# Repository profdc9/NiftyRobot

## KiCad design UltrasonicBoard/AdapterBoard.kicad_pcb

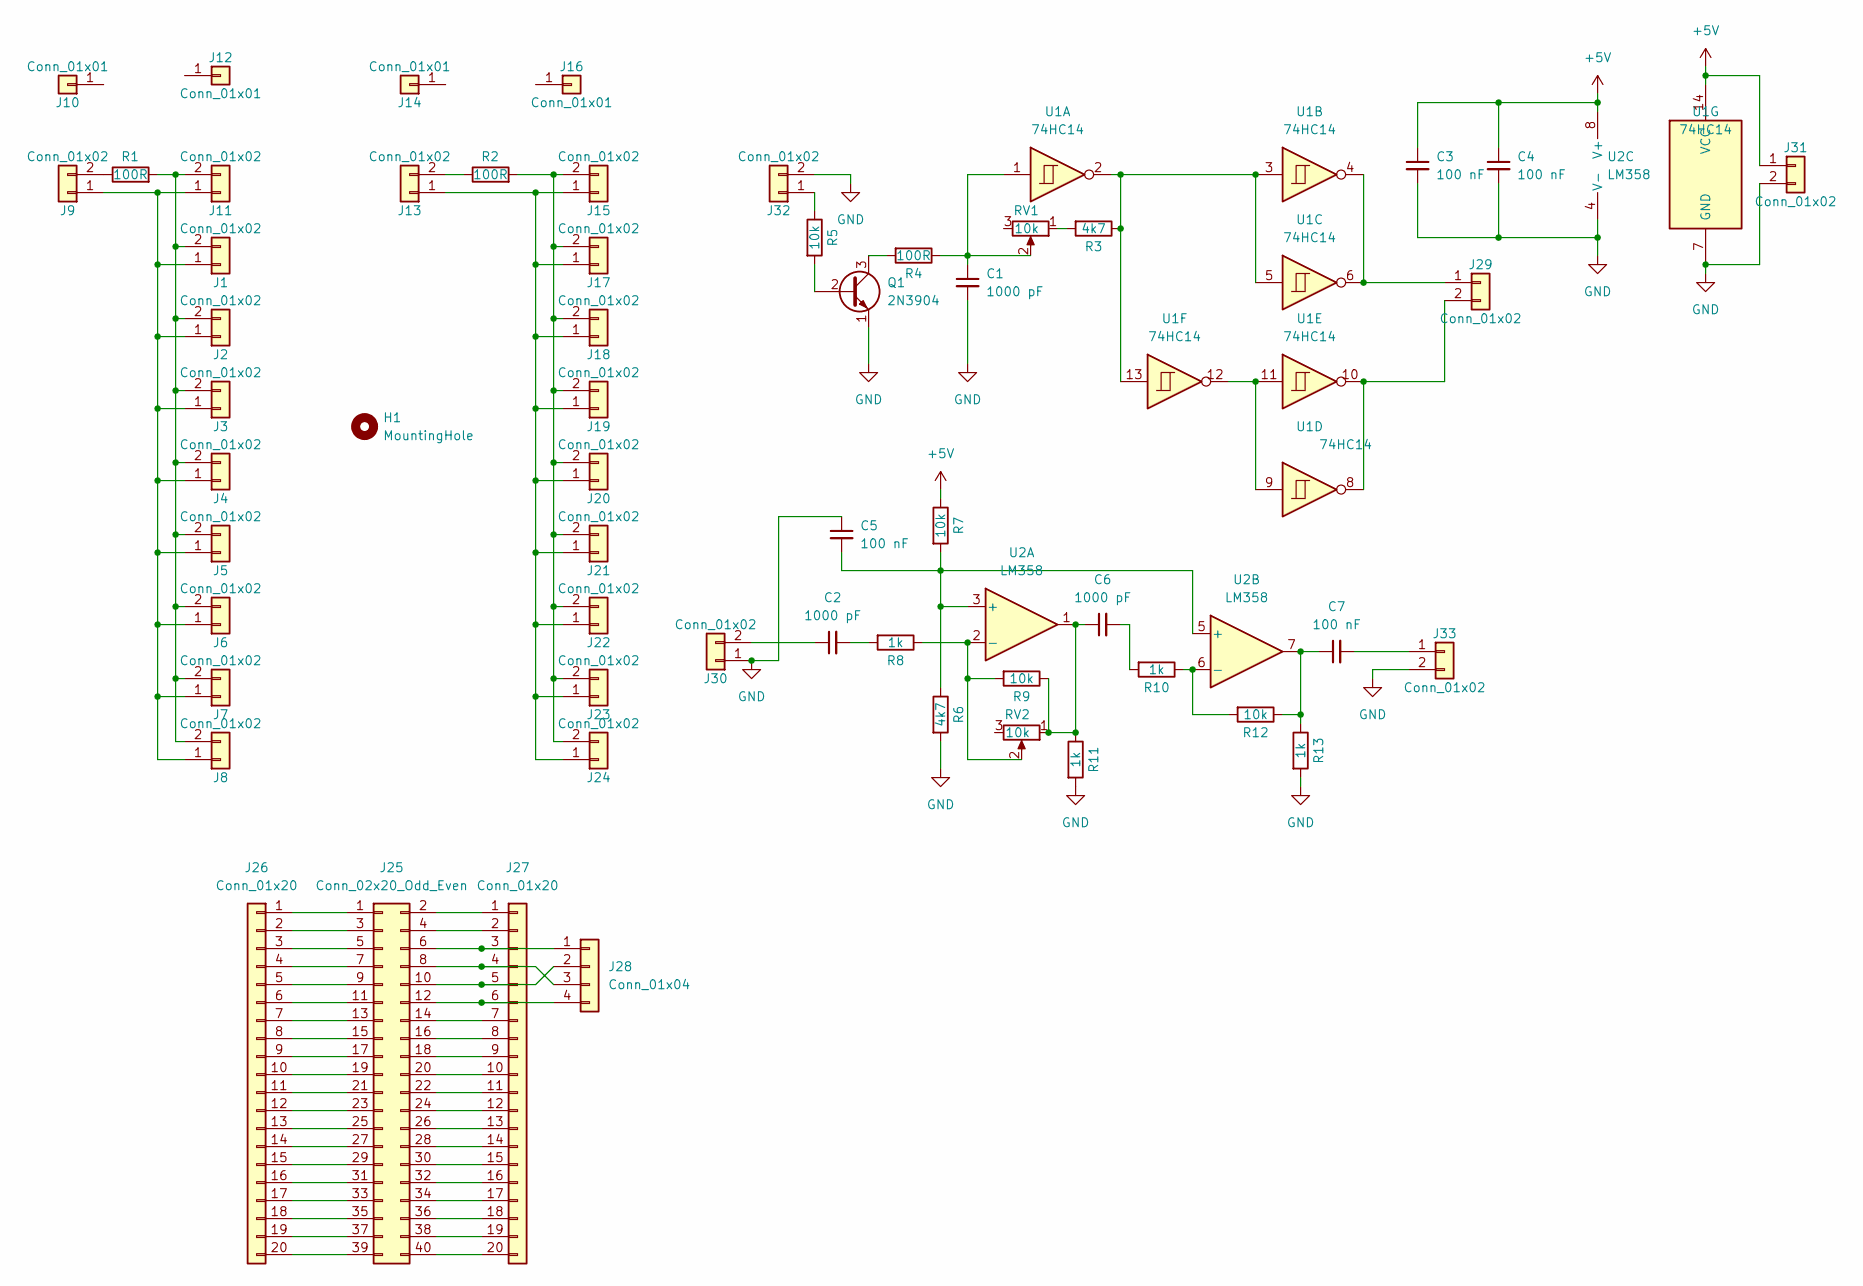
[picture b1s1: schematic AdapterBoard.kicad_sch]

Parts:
C1, C2, C6: 1000 pF; C_Disc_D5.0mm_W2.5mm_P5.00mm
C3, C4, C5, C7: 100 nF; C_Disc_D5.0mm_W2.5mm_P5.00mm
H1: MountingHole; BigSlotSeparator
J1, J2, J3, J4, J5, J6, J7, J8, J11, J15, J17, J18, J19, J20, J21, J22, J23, J24: Conn_01x02; UltrasoundTransceiver
J9, J13: Conn_01x02; TerminalBlock_bornier-2_P5.08mm
J10, J12, J14, J16: Conn_01x01; BlankMountingHole3.2
J25: Conn_02x20_Odd_Even; PinSocket_2x20_P2.54mm_Vertical
J26, J27: Conn_01x20; PinSocket_1x20_P2.54mm_Vertical
J28: Conn_01x04; PinSocket_1x04_P2.54mm_Vertical
J29, J30, J31, J32, J33: Conn_01x02; PinHeader_1x02_P2.54mm_Vertical
Q1: 2N3904; TO-92_Inline_Wide
R1, R2: 100R; R_Axial_DIN0414_L11.9mm_D4.5mm_P15.24mm_Horizontal
R3, R6: 4k7; R_Axial_DIN0207_L6.3mm_D2.5mm_P7.62mm_Horizontal
R4: 100R; R_Axial_DIN0207_L6.3mm_D2.5mm_P7.62mm_Horizontal
R5, R7, R9, R12: 10k; R_Axial_DIN0207_L6.3mm_D2.5mm_P7.62mm_Horizontal
R8, R10, R11, R13: 1k; R_Axial_DIN0207_L6.3mm_D2.5mm_P7.62mm_Horizontal
RV1, RV2: 10k; Potentiometer_Bourns_3296W_Vertical
U1: 74HC14; DIP-14_W7.62mm_Socket
U2: LM358; DIP-8_W7.62mm_Socket

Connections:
+5V: C3.1, C4.1, J31.1, R7.1, U1.14 (VCC), U2.8 (V+)
GND: C1.2, C3.2, C4.2, C5.1, J30.1, J31.2, J32.2, J33.2, Q1.1 (E), R6.2, R11.2, R13.2, U1.7 (GND), U2.4 (V-)
unnamed: C1.1, R4.1, RV1.2, U1.1
unnamed: C2.2, R8.2
unnamed: C6.1, R9.1, R11.1, RV2.1, U2.1
unnamed: C6.2, R10.2
unnamed: C7.1, R12.1, R13.1, U2.7
unnamed: J1.1, J2.1, J3.1, J4.1, J5.1, J6.1, J7.1, J8.1, J9.1, J11.1
unnamed: J1.2, J2.2, J3.2, J4.2, J5.2, J6.2, J7.2, J8.2, J11.2, R1.2
unnamed: J9.2, R1.1
unnamed: J13.1, J15.1, J17.1, J18.1, J19.1, J20.1, J21.1, J22.1, J23.1, J24.1
unnamed: J13.2, R2.1
unnamed: J15.2, J17.2, J18.2, J19.2, J20.2, J21.2, J22.2, J23.2, J24.2, R2.2
unnamed: J25.1, J26.1
unnamed: J25.2, J27.1
unnamed: J25.3, J26.2
unnamed: J25.4, J27.2
unnamed: J25.5, J26.3
unnamed: J25.6, J27.3, J28.1
unnamed: J25.7, J26.4
unnamed: J25.8, J27.4, J28.3
unnamed: J25.9, J26.5
unnamed: J25.10, J27.5, J28.2
unnamed: J25.11, J26.6
unnamed: J25.12, J27.6, J28.4
unnamed: J25.13, J26.7
unnamed: J25.14, J27.7
unnamed: J25.15, J26.8
unnamed: J25.16, J27.8
unnamed: J25.17, J26.9
unnamed: J25.18, J27.9
unnamed: J25.19, J26.10
unnamed: J25.20, J27.10
unnamed: J25.21, J26.11
unnamed: J25.22, J27.11
unnamed: J25.23, J26.12
unnamed: J25.24, J27.12
unnamed: J25.25, J26.13
unnamed: J25.26, J27.13
unnamed: J25.27, J26.14
unnamed: J25.28, J27.14
unnamed: J25.29, J26.15
unnamed: J25.30, J27.15
unnamed: J25.31, J26.16
unnamed: J25.32, J27.16
unnamed: J25.33, J26.17
unnamed: J25.34, J27.17
unnamed: J25.35, J26.18
unnamed: J25.36, J27.18
unnamed: J25.37, J26.19
unnamed: J25.38, J27.19
unnamed: J25.39, J26.20
unnamed: J25.40, J27.20
unnamed: J29.1, U1.4, U1.6
unnamed: J29.2, U1.8, U1.10
unnamed: C2.1, J30.2
unnamed: J32.1, R5.1
unnamed: C7.2, J33.1
unnamed: Q1.2 (B), R5.2
unnamed: Q1.3 (C), R4.2
unnamed: R3.1, U1.2, U1.3, U1.5, U1.13
unnamed: R3.2, RV1.1
unnamed: U1.9, U1.11, U1.12
unnamed: C5.2, R6.1, R7.2, U2.3 (+), U2.5 (+)
unnamed: R8.1, R9.2, RV2.2, U2.2 (-)
unnamed: R10.1, R12.2, U2.6 (-)

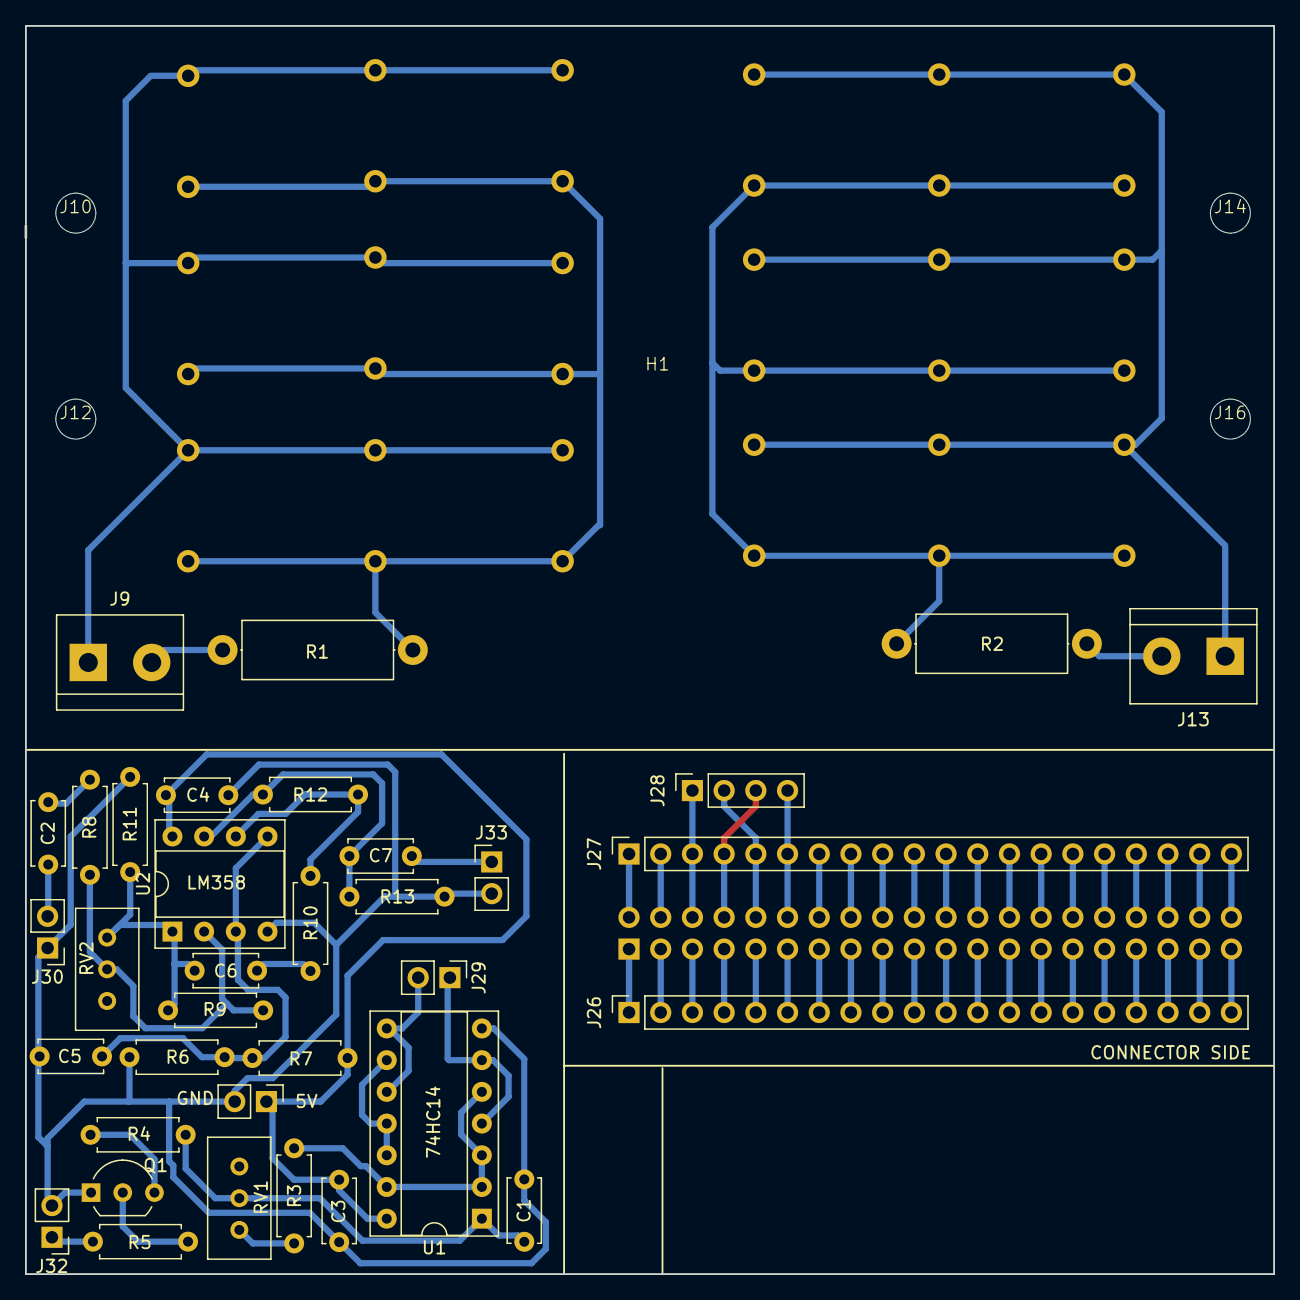
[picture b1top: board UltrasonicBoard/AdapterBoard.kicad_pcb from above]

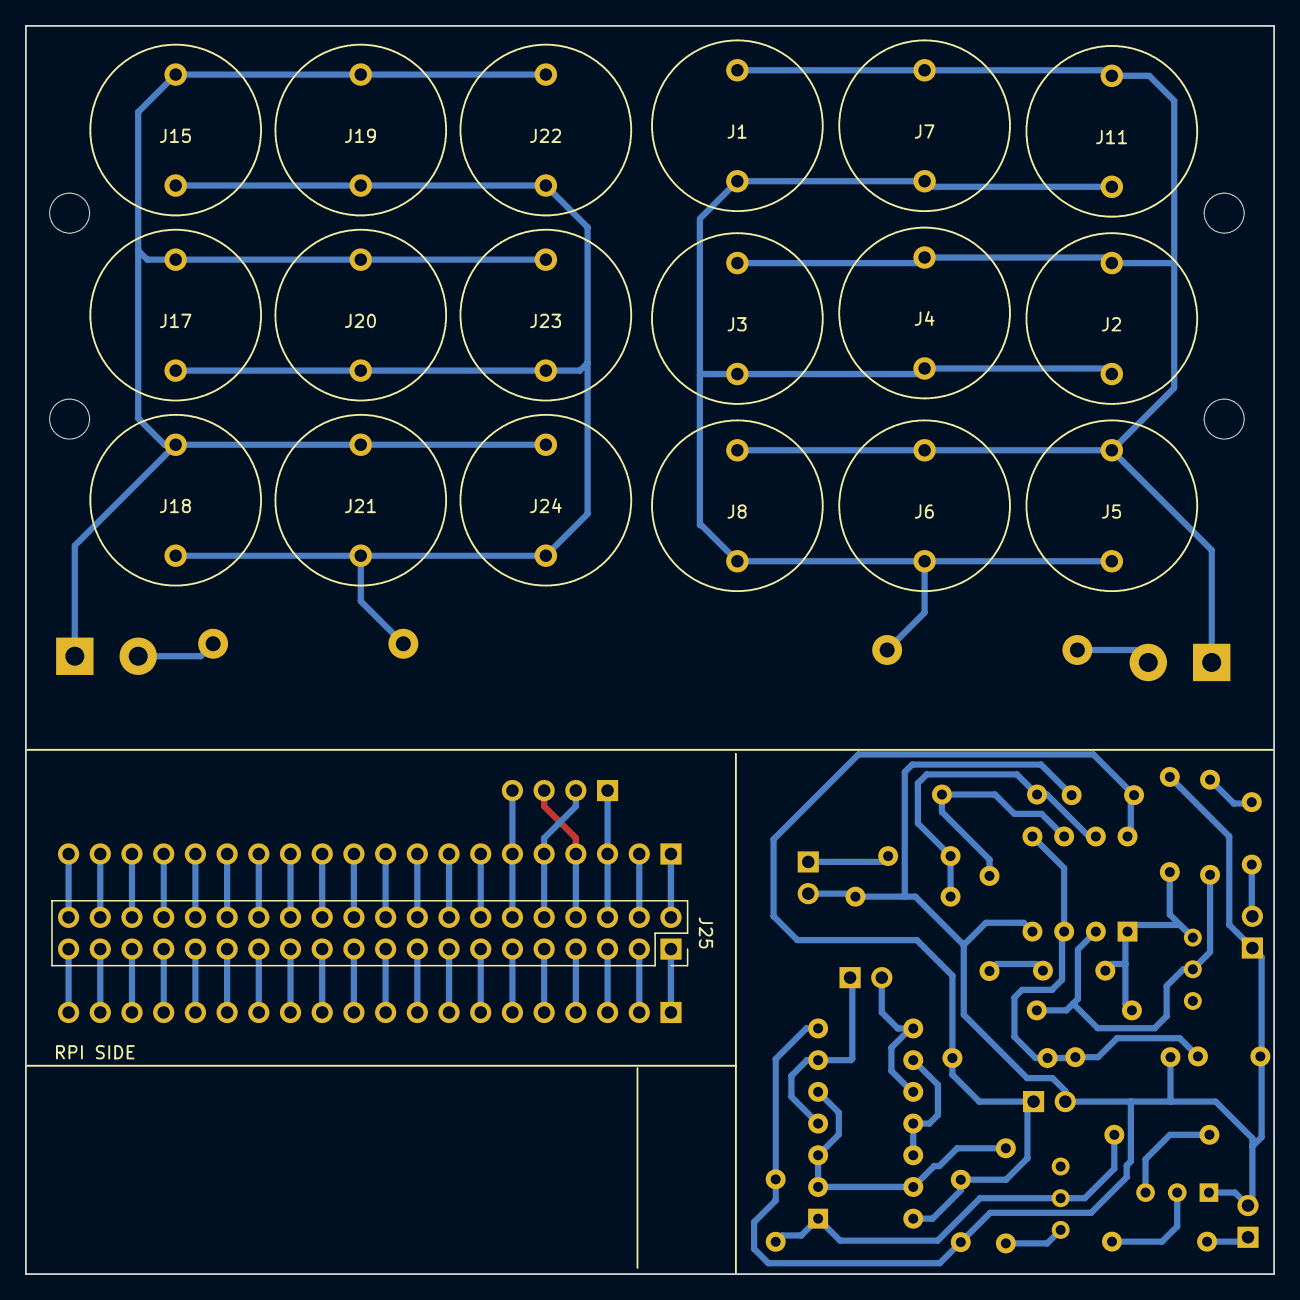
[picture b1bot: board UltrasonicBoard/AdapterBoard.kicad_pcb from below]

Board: 2 copper layers, 100.0 x 100.0 mm, 59 parts (19 on the bottom side), 66 nets.

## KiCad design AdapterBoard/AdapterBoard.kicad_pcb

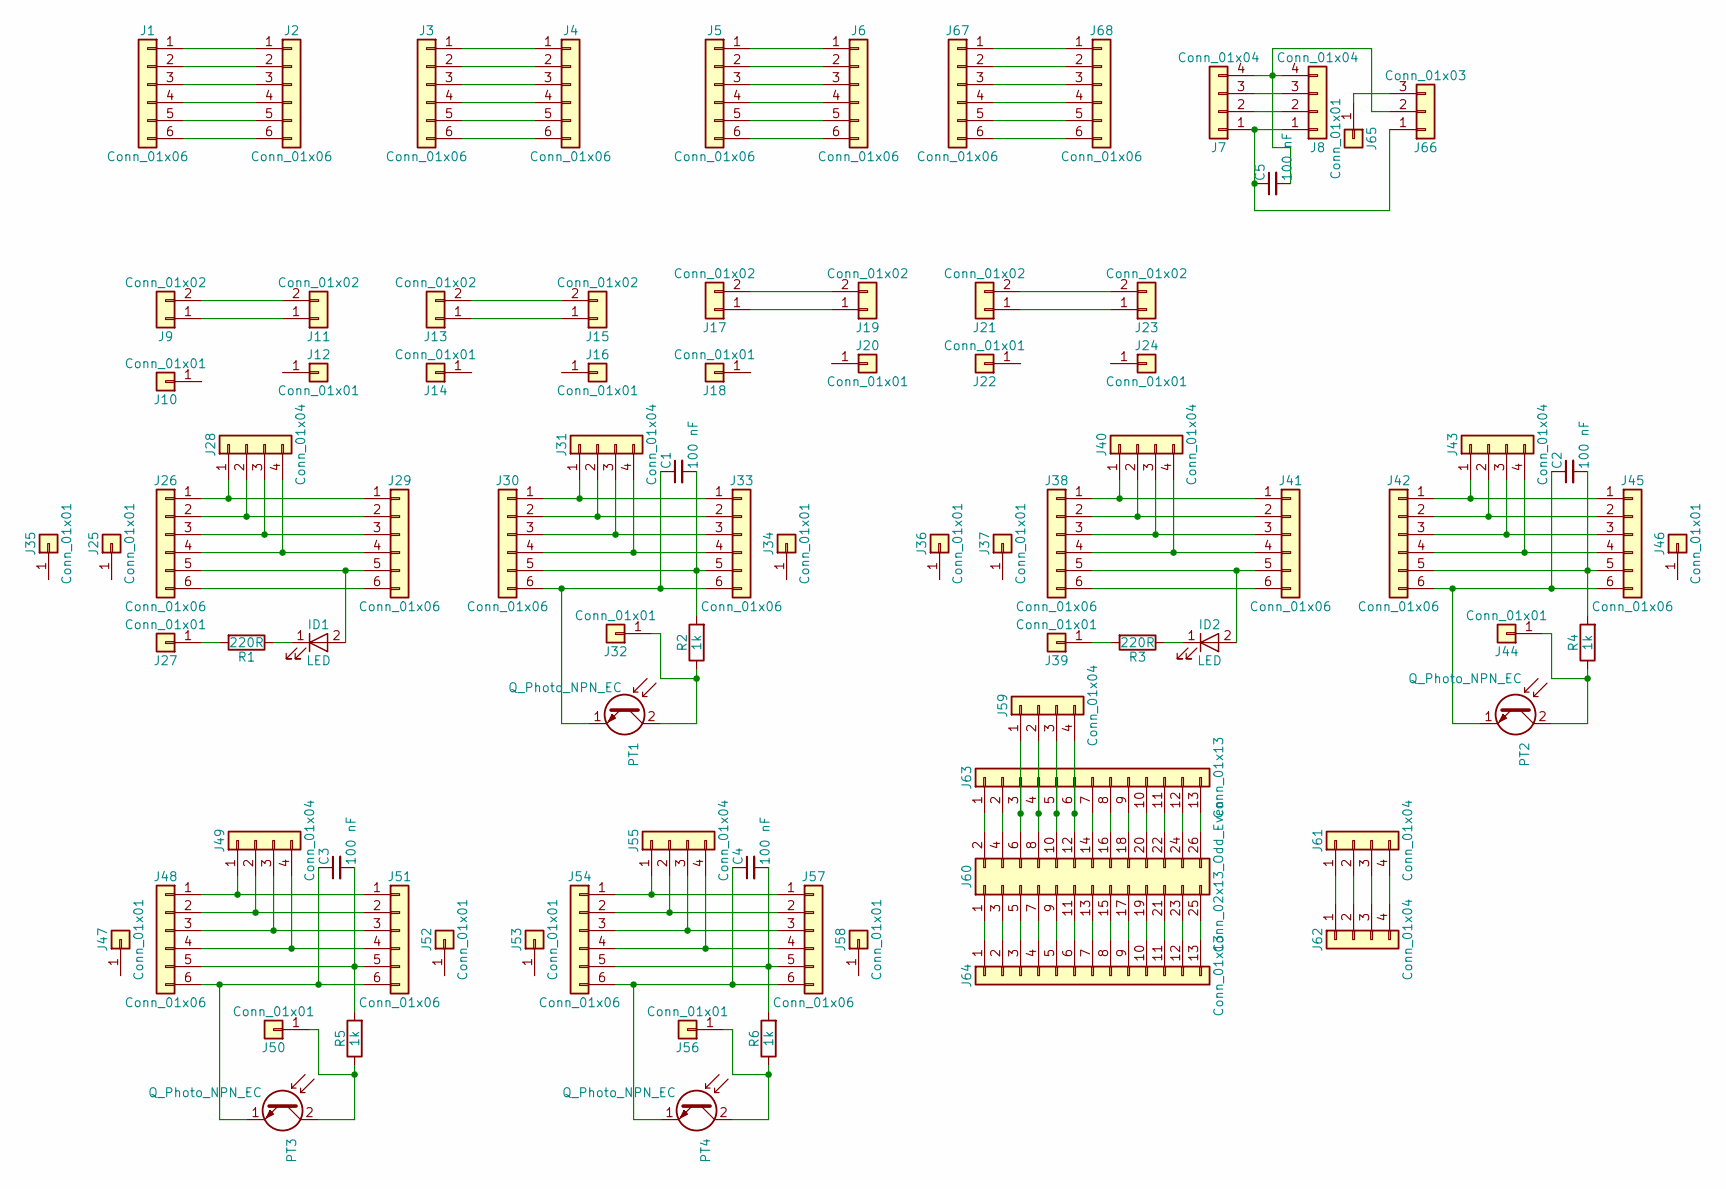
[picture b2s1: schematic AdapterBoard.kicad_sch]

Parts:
C1, C2, C3, C4, C5: 100 nF; C_Disc_D5.0mm_W2.5mm_P2.50mm
ID1, ID2: LED; LED_D5.0mm
J1, J2, J3, J4, J5, J6, J26, J29, J30, J33, J38, J41, J42, J45, J48, J51, J54, J57, J67, J68: Conn_01x06; Pin_Header_Straight_1x06_Pitch2.54mm
J7, J8, J28, J31, J40, J43, J49, J55, J59, J61, J62: Conn_01x04; Pin_Header_Straight_1x04_Pitch2.54mm
J9, J13, J17, J21: Conn_01x02; TerminalBlock_bornier-2_P5.08mm
J10, J12, J14, J16, J18, J20, J22, J24, J25, J34, J37, J46, J47, J52, J53, J58: Conn_01x01; 1pin
J11, J15, J19, J23: Conn_01x02; UltrasoundTransceiver
J27, J32, J39, J44, J50, J56, J65: Conn_01x01; Pin_Header_Straight_1x01_Pitch2.54mm
J35, J36: Conn_01x01; IRPair
J60: Conn_02x13_Odd_Even; Pin_Header_Straight_2x13_Pitch2.54mm
J63, J64: Conn_01x13; Pin_Header_Straight_1x13_Pitch2.54mm
J66: Conn_01x03; TO-92_Inline_Wide
PT1, PT2, PT3, PT4: Q_Photo_NPN_EC; LED_D5.0mm
R1, R3: 220R; R_Axial_DIN0207_L6.3mm_D2.5mm_P7.62mm_Horizontal
R2, R4, R5, R6: 1k; R_Axial_DIN0207_L6.3mm_D2.5mm_P7.62mm_Horizontal

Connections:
unnamed: C1.1, J30.6, J33.6, PT1.1 (E)
unnamed: C1.2, J30.5, J33.5, R2.2
unnamed: C2.1, J42.6, J45.6, PT2.1 (E)
unnamed: C2.2, J42.5, J45.5, R4.2
unnamed: C3.1, J48.6, J51.6, PT3.1 (E)
unnamed: C3.2, J48.5, J51.5, R5.2
unnamed: C4.1, J54.6, J57.6, PT4.1 (E)
unnamed: C4.2, J54.5, J57.5, R6.2
unnamed: C5.1, J7.1, J8.1, J66.1
unnamed: C5.2, J7.4, J8.4, J66.2
unnamed: ID1.1 (K), R1.1
unnamed: ID1.2 (A), J26.5, J29.5
unnamed: ID2.1 (K), R3.1
unnamed: ID2.2 (A), J38.5, J41.5
unnamed: J1.1, J2.1
unnamed: J1.2, J2.2
unnamed: J1.3, J2.3
unnamed: J1.4, J2.4
unnamed: J1.5, J2.5
unnamed: J1.6, J2.6
unnamed: J3.1, J4.1
unnamed: J3.2, J4.2
unnamed: J3.3, J4.3
unnamed: J3.4, J4.4
unnamed: J3.5, J4.5
unnamed: J3.6, J4.6
unnamed: J5.1, J6.1
unnamed: J5.2, J6.2
unnamed: J5.3, J6.3
unnamed: J5.4, J6.4
unnamed: J5.5, J6.5
unnamed: J5.6, J6.6
unnamed: J7.2, J8.2
unnamed: J7.3, J8.3
unnamed: J9.1, J11.1
unnamed: J9.2, J11.2
unnamed: J13.1, J15.1
unnamed: J13.2, J15.2
unnamed: J17.1, J19.1
unnamed: J17.2, J19.2
unnamed: J21.1, J23.1
unnamed: J21.2, J23.2
unnamed: J26.1, J28.1, J29.1
unnamed: J26.2, J28.2, J29.2
unnamed: J26.3, J28.3, J29.3
unnamed: J26.4, J28.4, J29.4
unnamed: J26.6, J29.6
unnamed: J27.1, R1.2
unnamed: J30.1, J31.1, J33.1
unnamed: J30.2, J31.2, J33.2
unnamed: J30.3, J31.3, J33.3
unnamed: J30.4, J31.4, J33.4
unnamed: J32.1, PT1.2 (C), R2.1
unnamed: J38.1, J40.1, J41.1
unnamed: J38.2, J40.2, J41.2
unnamed: J38.3, J40.3, J41.3
unnamed: J38.4, J40.4, J41.4
unnamed: J38.6, J41.6
unnamed: J39.1, R3.2
unnamed: J42.1, J43.1, J45.1
unnamed: J42.2, J43.2, J45.2
unnamed: J42.3, J43.3, J45.3
unnamed: J42.4, J43.4, J45.4
unnamed: J44.1, PT2.2 (C), R4.1
unnamed: J48.1, J49.1, J51.1
unnamed: J48.2, J49.2, J51.2
unnamed: J48.3, J49.3, J51.3
unnamed: J48.4, J49.4, J51.4
unnamed: J50.1, PT3.2 (C), R5.1
unnamed: J54.1, J55.1, J57.1
unnamed: J54.2, J55.2, J57.2
unnamed: J54.3, J55.3, J57.3
unnamed: J54.4, J55.4, J57.4
unnamed: J56.1, PT4.2 (C), R6.1
unnamed: J59.1, J60.6, J63.3
unnamed: J59.2, J60.8, J63.4
unnamed: J59.3, J60.10, J63.5
unnamed: J59.4, J60.12, J63.6
unnamed: J60.1, J64.1
unnamed: J60.2, J63.1
unnamed: J60.3, J64.2
unnamed: J60.4, J63.2
unnamed: J60.5, J64.3
unnamed: J60.7, J64.4
unnamed: J60.9, J64.5
unnamed: J60.11, J64.6
unnamed: J60.13, J64.7
unnamed: J60.14, J63.7
unnamed: J60.15, J64.8
unnamed: J60.16, J63.8
unnamed: J60.17, J64.9
unnamed: J60.18, J63.9
unnamed: J60.19, J64.10
unnamed: J60.20, J63.10
unnamed: J60.21, J64.11
unnamed: J60.22, J63.11
unnamed: J60.23, J64.12
unnamed: J60.24, J63.12
unnamed: J60.25, J64.13
unnamed: J60.26, J63.13
unnamed: J61.1, J62.1
unnamed: J61.2, J62.2
unnamed: J61.3, J62.3
unnamed: J61.4, J62.4
unnamed: J65.1, J66.3
unnamed: J67.1, J68.1
unnamed: J67.2, J68.2
unnamed: J67.3, J68.3
unnamed: J67.4, J68.4
unnamed: J67.5, J68.5
unnamed: J67.6, J68.6

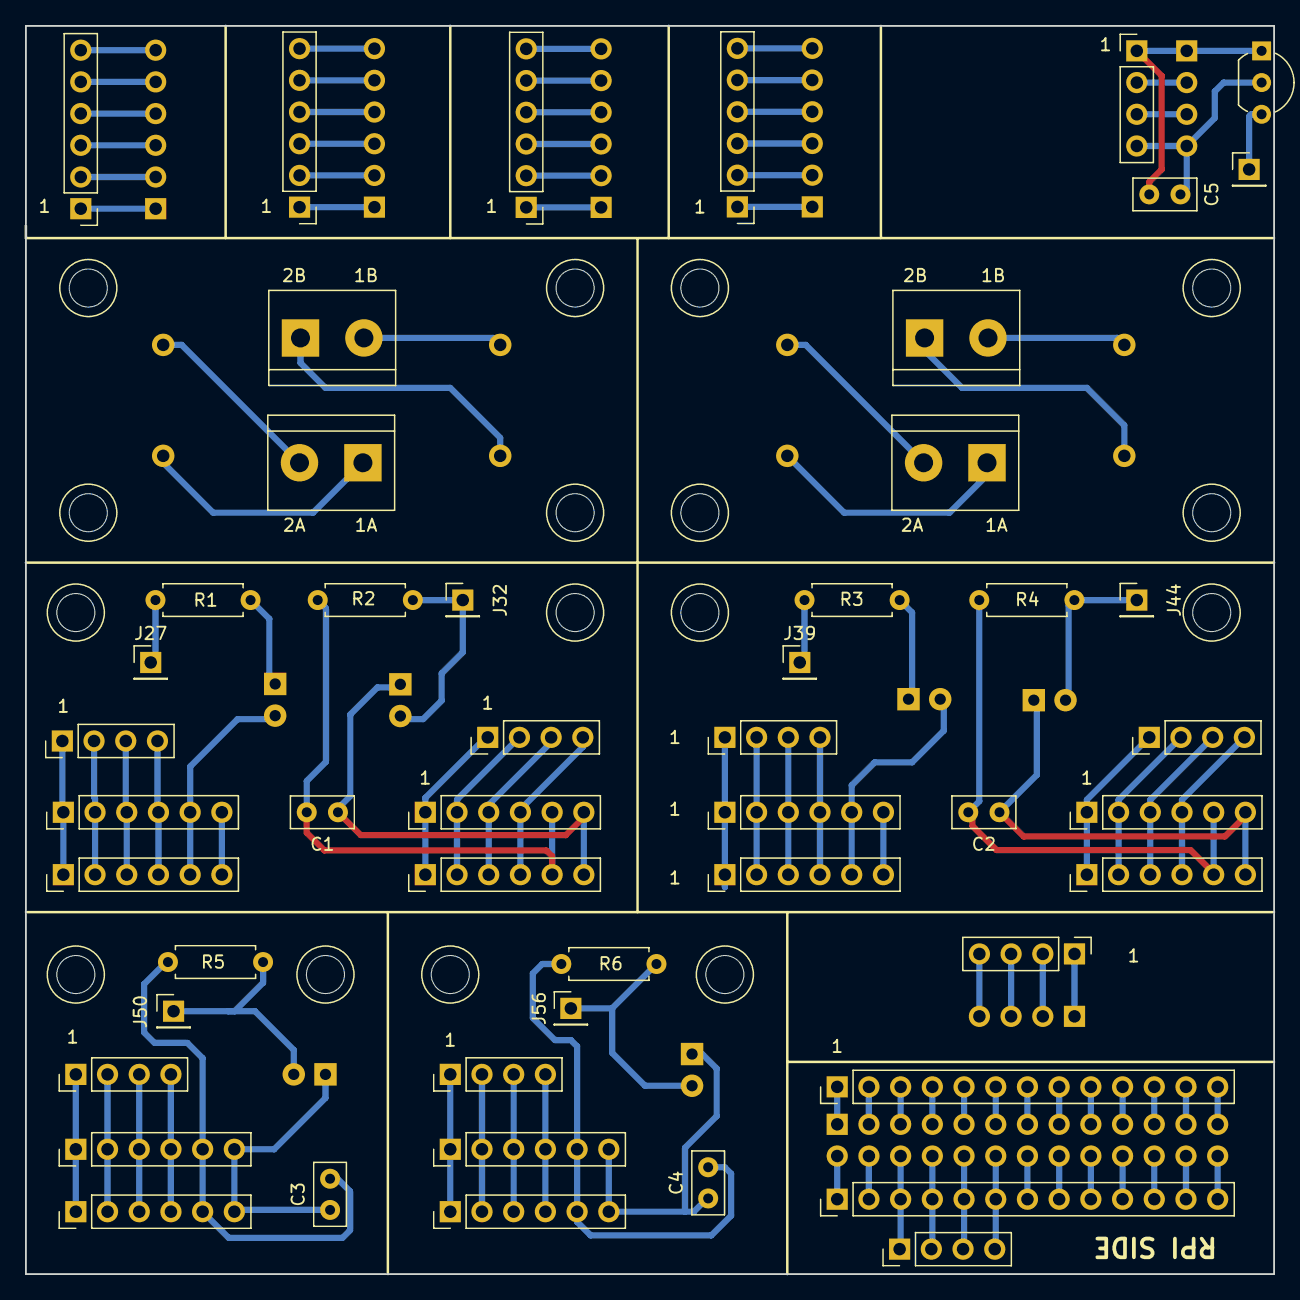
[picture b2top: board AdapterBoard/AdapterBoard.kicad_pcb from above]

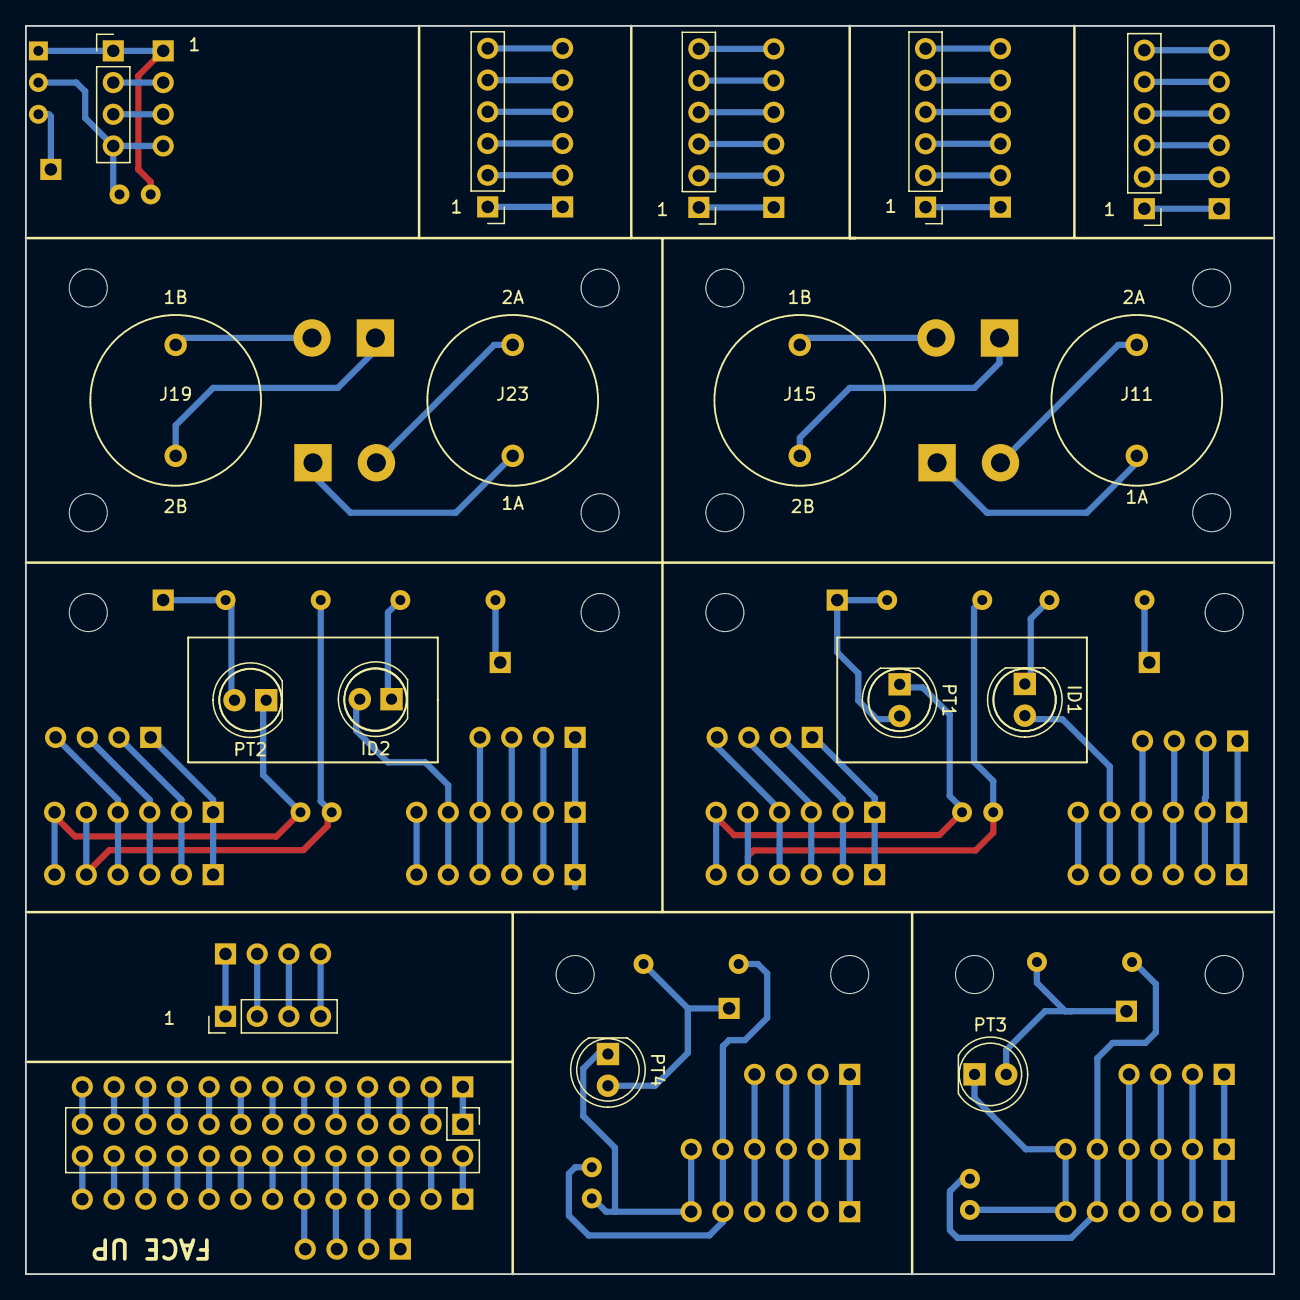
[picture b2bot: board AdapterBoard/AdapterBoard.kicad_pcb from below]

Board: 2 copper layers, 100.0 x 100.0 mm, 85 parts (19 on the bottom side), 111 nets.

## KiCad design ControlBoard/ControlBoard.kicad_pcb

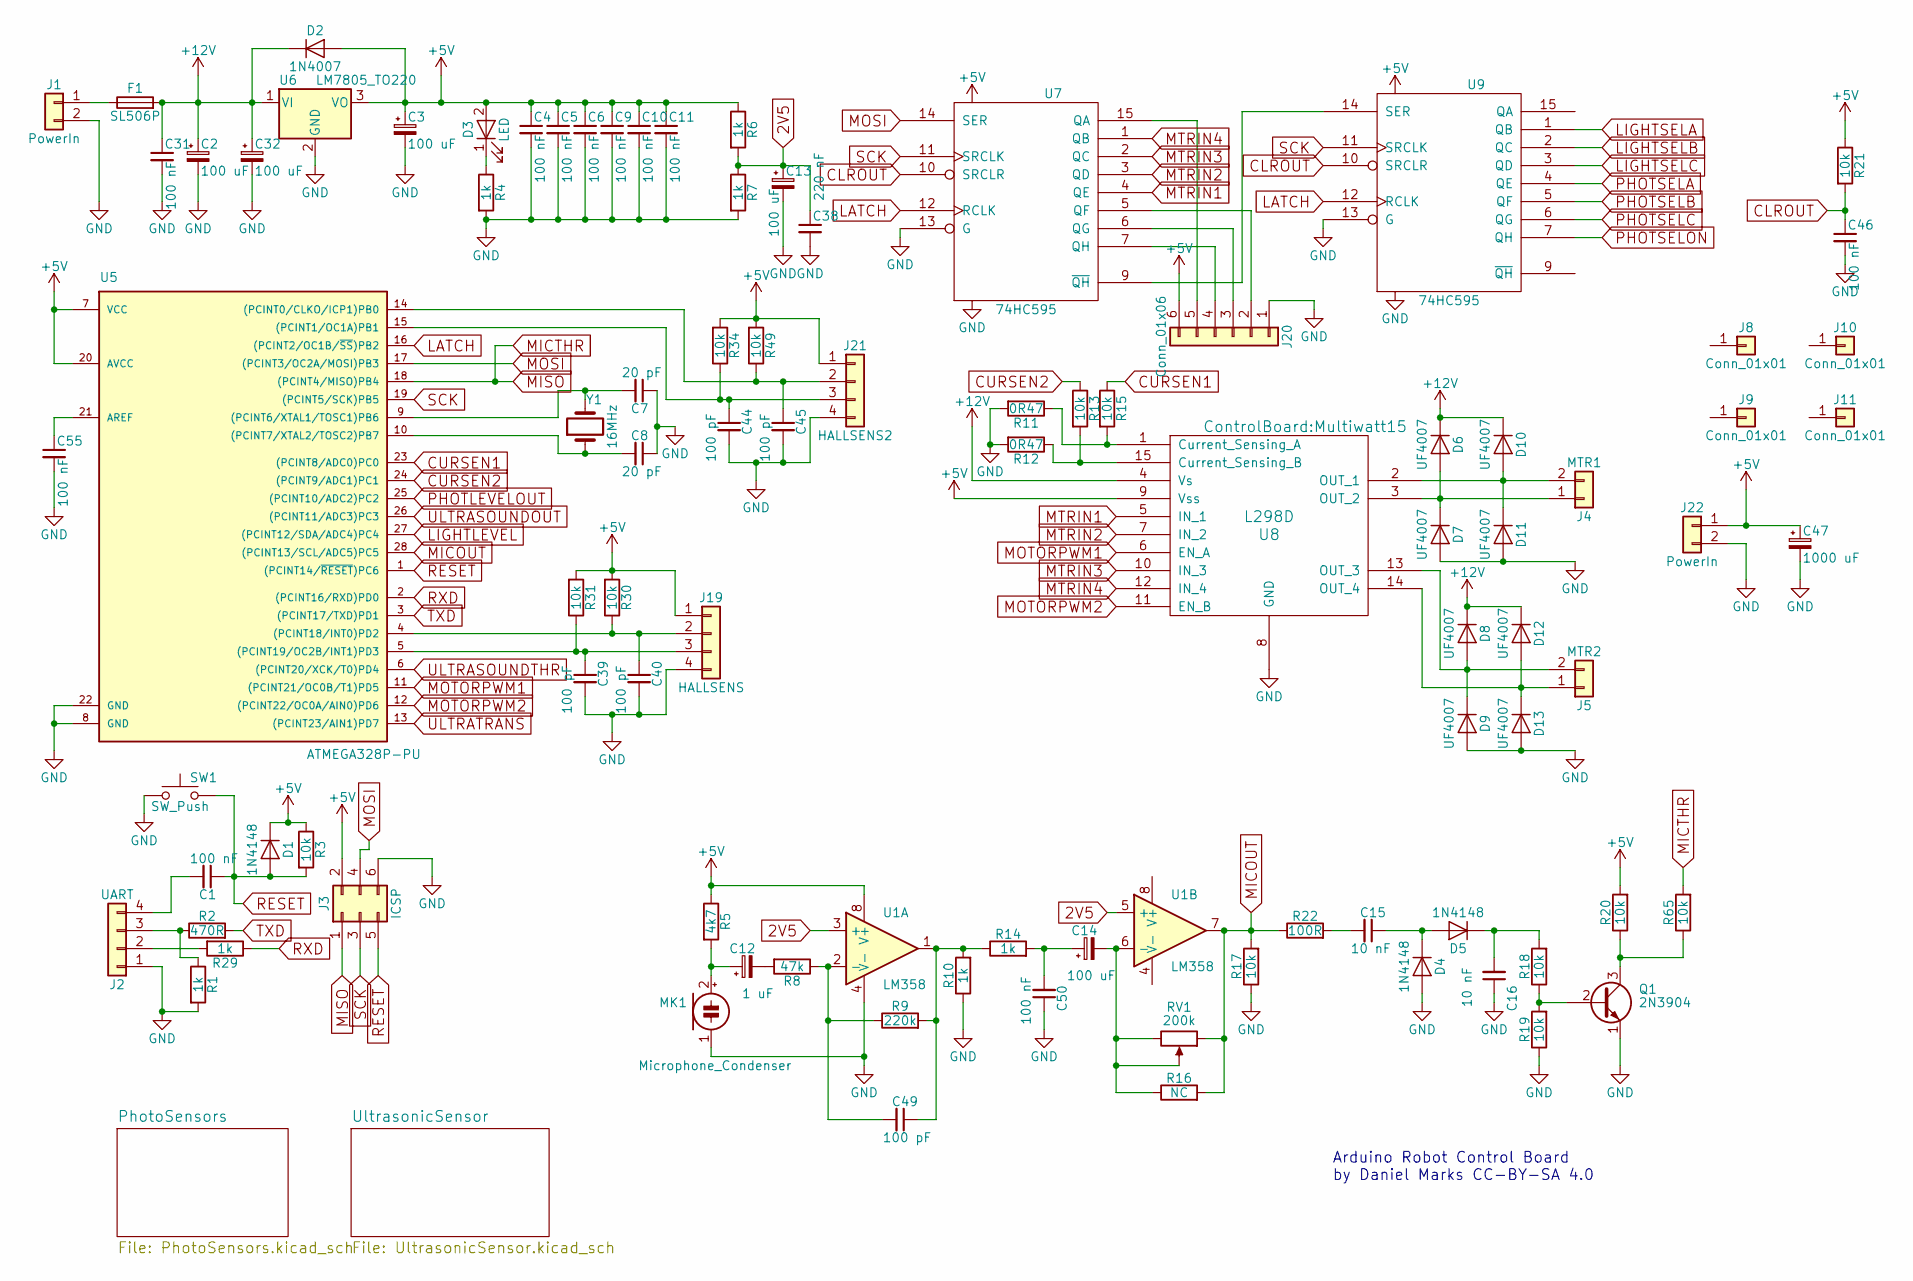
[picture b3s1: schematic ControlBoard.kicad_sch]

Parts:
C1, C4, C5, C6, C9, C10, C11, C31, C46, C55: 100 nF; C_Disc_D5.0mm_W2.5mm_P2.50mm
C2, C3, C13, C14, C32: 100 uF; CP_Radial_D5.0mm_P2.50mm
C7, C8: 20 pF; C_Disc_D5.0mm_W2.5mm_P5.00mm
C12: 1 uF; CP_Radial_D5.0mm_P2.50mm
C15, C16: 10 nF; C_Disc_D5.0mm_W2.5mm_P5.00mm
C38: 220 nF; C_Disc_D5.0mm_W2.5mm_P2.50mm
C39, C40, C44, C45, C49: 100 pF; C_Disc_D5.0mm_W2.5mm_P5.00mm
C47: 1000 uF; CP_Radial_D7.5mm_P2.50mm
C50: 100 nF; C_Disc_D5.0mm_W2.5mm_P5.00mm
D1: 1N4148; D_DO-35_SOD27_P7.62mm_Horizontal
D2: 1N4007; D_DO-41_SOD81_P7.62mm_Horizontal
D3: LED; LED_D5.0mm
D4, D5: 1N4148; D_DO-41_SOD81_P7.62mm_Horizontal
D6, D7, D8, D9, D10, D11, D12, D13: UF4007; D_DO-41_SOD81_P7.62mm_Horizontal
F1: SL506P; SL506Pfuseholder
J1, J22: PowerIn; TerminalBlock_bornier-2_P5.08mm
J2: UART; Pin_Header_Straight_1x04_Pitch2.54mm
J3: ICSP; Pin_Header_Straight_2x03_Pitch2.54mm
J4: MTR1; TerminalBlock_bornier-2_P5.08mm
J5: MTR2; TerminalBlock_bornier-2_P5.08mm
J8, J9, J10, J11: Conn_01x01; 1pin
J19: HALLSENS; Pin_Header_Straight_1x04_Pitch2.54mm
J20: Conn_01x06; Pin_Header_Straight_1x06_Pitch2.54mm
J21: HALLSENS2; Pin_Header_Straight_1x04_Pitch2.54mm
MK1: Microphone_Condenser; CondenserMic
Q1: 2N3904; TO-92_Inline_Wide
R1, R4, R6, R7, R10, R14, R29: 1k; R_Axial_DIN0207_L6.3mm_D2.5mm_P7.62mm_Horizontal
R2: 470R; R_Axial_DIN0207_L6.3mm_D2.5mm_P7.62mm_Horizontal
R3, R13, R15, R17, R18, R19, R20, R21, R30, R31, R34, R49, R65: 10k; R_Axial_DIN0207_L6.3mm_D2.5mm_P7.62mm_Horizontal
R5: 4k7; R_Axial_DIN0207_L6.3mm_D2.5mm_P7.62mm_Horizontal
R8: 47k; R_Axial_DIN0207_L6.3mm_D2.5mm_P7.62mm_Horizontal
R9: 220k; R_Axial_DIN0207_L6.3mm_D2.5mm_P7.62mm_Horizontal
R11, R12: 0R47; R_Axial_DIN0414_L11.9mm_D4.5mm_P20.32mm_Horizontal
R16: NC; R_Axial_DIN0207_L6.3mm_D2.5mm_P7.62mm_Horizontal
R22: 100R; R_Axial_DIN0207_L6.3mm_D2.5mm_P7.62mm_Horizontal
RV1: 200k; Potentiometer_Trimmer_Bourns_3296W
SW1: SW_Push; SW_PUSH_6mm
U1: LM358; DIP-8_W7.62mm_Socket
U5: ATMEGA328P-PU; DIP-28_W7.62mm_Socket
U6: LM7805_TO220; TO-220-3_Vertical
U7, U9: 74HC595; DIP-16_W7.62mm_Socket
U8: L298D; Multiwatt15
Y1: 16MHz; Crystal_HC49-U_Vertical

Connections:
2V5: C13.1, C38.1, R6.2, R7.1, U1.3 (+), U1.5 (+); also elsewhere on the board
+5V: C3.1, C4.1, C5.1, C6.1, C9.1, C10.1, C11.1, C47.1, D1.1 (K), D2.2 (A), D3.2 (A), J3.2, J19.1, J20.6, J21.1, J22.1, R3.1, R5.1, R6.1, R20.2, R21.1, R30.2, R31.2, R34.2, R49.2, U1.8 (V+), U5.7 (VCC), U5.20 (AVCC), U6.3 (VO), U7.16 (VCC), U8.9 (Vss), U9.16 (VCC); also elsewhere on the board
+12V: C2.1, C31.1, C32.1, D2.1 (K), D6.1 (K), D8.1 (K), D10.1 (K), D12.1 (K), F1.2, U6.1 (VI), U8.4 (Vs)
CLROUT: C46.1, R21.2, U7.10 (SRCLR), U9.10 (SRCLR)
CURSEN1: R15.1, U5.23 ((PCINT8/ADC0)PC0)
CURSEN2: R13.1, U5.24 ((PCINT9/ADC1)PC1)
GND: C2.2, C3.2, C4.2, C5.2, C6.2, C7.1, C8.1, C9.2, C10.2, C11.2, C13.2, C16.1, C31.2, C32.2, C38.2, C39.2, C40.2, C44.2, C45.2, C46.2, C47.2, C50.1, C55.2, D4.2 (A), D7.2 (A), D9.2 (A), D11.2 (A), D13.2 (A), J1.2, J2.1, J3.6, J19.4, J20.1, J21.4, J22.2, MK1.1 (-), Q1.1 (E), R1.2, R4.2, R7.2, R10.1, R11.2, R12.2, R17.1, R19.1, SW1.1, U1.4 (V-), U5.8 (GND), U5.22 (GND), U6.2 (GND), U7.8 (GND), U7.13 (G), U8.8 (GND), U9.8 (GND), U9.13 (G); also elsewhere on the board
LATCH: U5.16 ((PCINT2/OC1B/~SS)PB2), U7.12 (RCLK), U9.12 (RCLK)
LIGHTLEVEL: U5.27 ((PCINT12/SDA/ADC4)PC4); also elsewhere on the board
LIGHTSELA: U9.1 (QB); also elsewhere on the board
LIGHTSELB: U9.2 (QC); also elsewhere on the board
LIGHTSELC: U9.3 (QD); also elsewhere on the board
MICOUT: R16.2, R17.2, R22.1, RV1.1, U1.7, U5.28 ((PCINT13/SCL/ADC5)PC5)
MICTHR: J3.1, R65.2, U5.18 ((PCINT4/MISO)PB4)
MOSI: J3.4, U5.17 ((PCINT3/OC2A/MOSI)PB3), U7.14 (SER)
MOTORPWM1: U5.11 ((PCINT21/OC0B/T1)PD5), U8.6 (EN_A)
MOTORPWM2: U5.12 ((PCINT22/OC0A/AIN0)PD6), U8.11 (EN_B)
MTRIN1: U7.4 (QE), U8.5 (IN_1)
MTRIN2: U7.3 (QD), U8.7 (IN_2)
MTRIN3: U7.2 (QC), U8.10 (IN_3)
MTRIN4: U7.1 (QB), U8.12 (IN_4)
unnamed: C12.2, R8.2
unnamed: C14.1, C50.2, R14.2
unnamed: C15.2, R22.2
unnamed: C49.1, R9.2, R10.2, R14.1, U1.1
unnamed: D3.1 (K), R4.1
unnamed: C15.1, D4.1 (K), D5.2 (A)
unnamed: C16.2, D5.1 (K), R18.2
unnamed: D6.2 (A), D7.1 (K), J4.1, U8.3 (OUT_2)
unnamed: D8.2 (A), D9.1 (K), J5.2, U8.13 (OUT_3)
unnamed: D10.2 (A), D11.1 (K), J4.2, U8.2 (OUT_1)
unnamed: D12.2 (A), D13.1 (K), J5.1, U8.14 (OUT_4)
unnamed: F1.1, J1.1
unnamed: J2.2, R29.2
unnamed: J2.3, R1.1, R2.1
unnamed: C1.2, J2.4
unnamed: C40.1, J19.2, R30.1, U5.4 ((PCINT18/INT0)PD2)
unnamed: C39.1, J19.3, R31.1, U5.5 ((PCINT19/OC2B/INT1)PD3)
unnamed: J20.2, U7.5 (QF)
unnamed: J20.3, U7.6 (QG)
unnamed: J20.4, U7.7 (QH)
unnamed: J20.5, U7.15 (QA)
unnamed: C45.1, J21.2, R49.1, U5.14 ((PCINT0/CLKO/ICP1)PB0)
unnamed: C44.1, J21.3, R34.1, U5.15 ((PCINT1/OC1A)PB1)
unnamed: C12.1, MK1.2 (+), R5.2
unnamed: Q1.2 (B), R18.1, R19.2
unnamed: Q1.3 (C), R20.1, R65.1
unnamed: C49.2, R8.1, R9.1, U1.2 (-)
unnamed: C14.2, R16.1, RV1.2, RV1.3, U1.6 (-)
unnamed: C7.2, U5.9 ((PCINT6/XTAL1/TOSC1)PB6), Y1.2
unnamed: C8.2, U5.10 ((PCINT7/XTAL2/TOSC2)PB7), Y1.1
unnamed: C55.1, U5.21 (AREF)
unnamed: U7.9 (~QH), U9.14 (SER)
unnamed: R11.1, R15.2, U8.1 (Current_Sensing_A)
unnamed: R12.1, R13.2, U8.15 (Current_Sensing_B)
PHOTLEVELOUT: U5.25 ((PCINT10/ADC2)PC2); also elsewhere on the board
PHOTSELA: U9.4 (QE); also elsewhere on the board
PHOTSELB: U9.5 (QF); also elsewhere on the board
PHOTSELC: U9.6 (QG); also elsewhere on the board
PHOTSELON: U9.7 (QH); also elsewhere on the board
RESET: C1.1, D1.2 (A), J3.5, R3.2, SW1.2, U5.1 ((PCINT14/~RESET)PC6)
RXD: R29.1, U5.2 ((PCINT16/RXD)PD0)
SCK: J3.3, U5.19 ((PCINT5/SCK)PB5), U7.11 (SRCLK), U9.11 (SRCLK)
TXD: R2.2, U5.3 ((PCINT17/TXD)PD1)
ULTRASOUNDOUT: U5.26 ((PCINT11/ADC3)PC3); also elsewhere on the board
ULTRASOUNDTHR: U5.6 ((PCINT20/XCK/T0)PD4); also elsewhere on the board
ULTRATRANS: U5.13 ((PCINT23/AIN1)PD7); also elsewhere on the board

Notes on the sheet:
Arduino Robot Control Board by Daniel Marks CC-BY-SA 4.0
